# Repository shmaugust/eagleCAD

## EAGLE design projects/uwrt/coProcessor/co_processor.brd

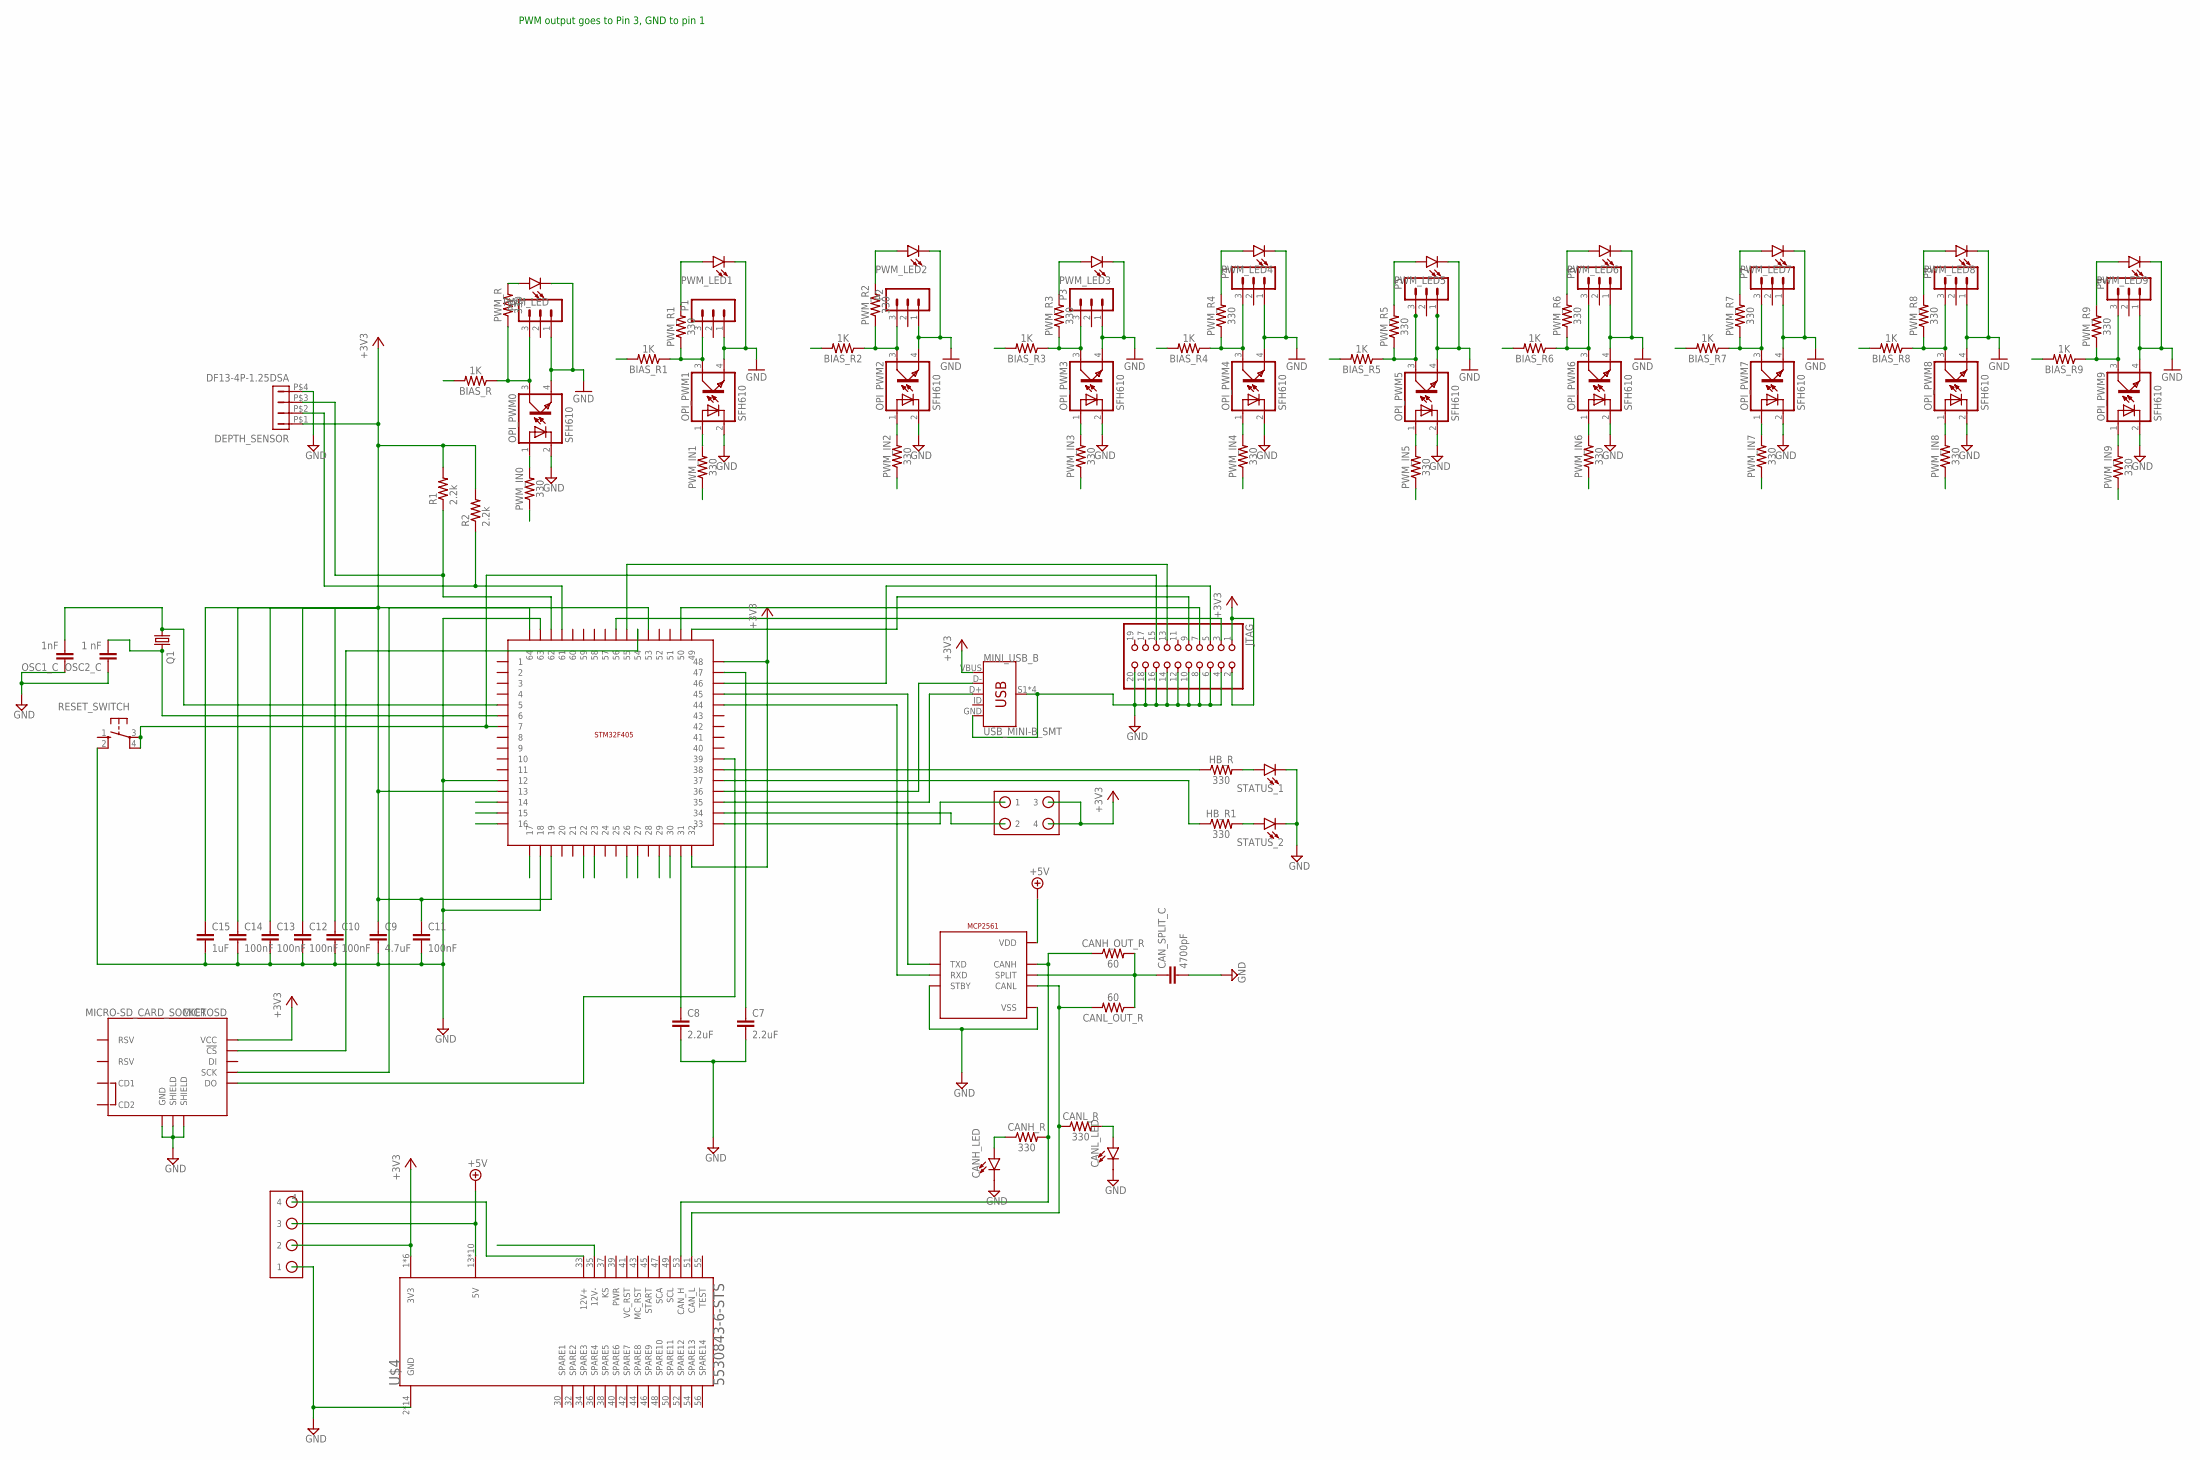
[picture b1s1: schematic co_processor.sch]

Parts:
BIAS_R, BIAS_R1, BIAS_R2, BIAS_R3, BIAS_R4, BIAS_R5, BIAS_R6, BIAS_R7, BIAS_R8, BIAS_R9: 1K; 0603
C7, C8: 2.2uF; C025-025X050
C9: 4.7uF; C025-025X050
C10, C11, C12, C13, C14: 100nF; C025-025X050
C15: 1uF; C025-025X050
CANH_LED: LED1206; LED-1206
CANH_OUT_R: 60; 0603
CANH_R: 330; 0603
CANL_LED: LED1206; LED-1206
CANL_OUT_R: 60; 0603
CANL_R: 330; 0603
CAN_SPLIT_C: 4700pF; C2.5-2
DEPTH_SENSOR: DF13-4P-1.25DSA
HB_R, HB_R1: 330; 0603
JTAG: PINHD-2X10; 2X10
MCP2561: MCP2561; SOIC8
MICROSD: MICRO-SD_CARD_SOCKET; MICRO-SD-SOCKET
MINI_USB_B: USB_MINI-B_SMT; USB-MINIB
OPI_PWM0, OPI_PWM1, OPI_PWM2, OPI_PWM3, OPI_PWM4, OPI_PWM5, OPI_PWM6, OPI_PWM7, OPI_PWM8, OPI_PWM9: SFH610; DIL04
OSC1_C: 1nF; C2.5-2
OSC2_C: 1 nF; C2.5-2
P0, P1, P2, P3, P4, P5, P6, P7, P8, P9: MA03-1
PWM_IN0, PWM_IN1, PWM_IN2, PWM_IN3, PWM_IN4, PWM_IN5, PWM_IN6, PWM_IN7, PWM_IN8, PWM_IN9: 330; 0603
PWM_LED, PWM_LED1, PWM_LED2, PWM_LED3, PWM_LED4, PWM_LED5, PWM_LED6, PWM_LED7, PWM_LED8, PWM_LED9: LED1206; LED-1206
PWM_R, PWM_R1, PWM_R2, PWM_R3, PWM_R4, PWM_R5, PWM_R6, PWM_R7, PWM_R8, PWM_R9: 330; 0603
Q1: CRYSTALHC49S; HC49/S
R1, R2: 2.2k; 0204/5
RESET_SWITCH: 10-XX; B3F-10XX
STATUS_1, STATUS_2: LED1206; LED-1206
STM32F405: STM32F405RG
SWITCHES: 39-30-1040; 5569-04A2
U$4: 5530843-6-STS; 5530843-6-BOARD
U$7: 70555-0003

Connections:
12V_OUT: BIAS_R.2, BIAS_R1.2, BIAS_R2.2, BIAS_R3.2, BIAS_R4.2, BIAS_R5.2, BIAS_R6.2, BIAS_R7.2, BIAS_R8.2, BIAS_R9.2, U$4.33 (12V+), U$7.4
+3V3: C9.1, C10.1, C11.1, C12.1, C13.1, C14.1, C15.1, DEPTH_SENSOR.P$1 (1), JTAG.1, JTAG.2, MICROSD.VCC, MINI_USB_B.VBUS, R1.2, R2.2, STM32F405.13, STM32F405.19, STM32F405.32, STM32F405.48, STM32F405.64, SWITCHES.1 (4), SWITCHES.2 (3), U$4.1 (3V3), U$4.3 (3V3), U$4.5 (3V3), U$4.7 (3V3), U$4.9 (3V3), U$4.11 (3V3), U$7.2
+5V: MCP2561.P$3 (VDD), U$4.13 (5V), U$4.15 (5V), U$4.17 (5V), U$4.19 (5V), U$4.21 (5V), U$4.23 (5V), U$4.25 (5V), U$4.27 (5V), U$4.29 (5V), U$4.31 (5V), U$7.3
CANH_LED: CANH_LED.A, CANH_R.1
CANH_OUT: CANH_OUT_R.1, CANH_R.2, MCP2561.P$7 (CANH), U$4.53 (CAN_H)
CANL_LED: CANL_LED.A, CANL_R.2
CANL_OUT: CANL_OUT_R.2, CANL_R.1, MCP2561.P$6 (CANL), U$4.51 (CAN_L)
CAN_RX: MCP2561.P$4 (RXD), STM32F405.44
CAN_SPLIT: CANH_OUT_R.2, CANL_OUT_R.1, CAN_SPLIT_C.1, MCP2561.P$5 (SPLIT)
CAN_TX: MCP2561.P$1 (TXD), STM32F405.45
GND: C7.2, C8.2, C9.2, C10.2, C11.2, C12.2, C13.2, C14.2, C15.2, CANH_LED.C, CANL_LED.C, CAN_SPLIT_C.2, DEPTH_SENSOR.P$4 (4), JTAG.4, JTAG.6, JTAG.8, JTAG.10, JTAG.12, JTAG.14, JTAG.16, JTAG.18, JTAG.20, MCP2561.P$2 (VSS), MCP2561.P$8 (STBY), MICROSD.GND, MICROSD.GND1 (SHIELD), MICROSD.GND3 (SHIELD), MINI_USB_B.GND, MINI_USB_B.S1 (SHIELD), MINI_USB_B.S2 (SHIELD), MINI_USB_B.S3 (SHIELD), MINI_USB_B.S4 (SHIELD), OPI_PWM0.2 (C), OPI_PWM1.2 (C), OPI_PWM2.2 (C), OPI_PWM3.2 (C), OPI_PWM4.2 (C), OPI_PWM5.2 (C), OPI_PWM6.2 (C), OPI_PWM7.2 (C), OPI_PWM8.2 (C), OPI_PWM9.2 (C), OSC1_C.1, OSC2_C.1, RESET_SWITCH.2 (S1), STATUS_1.C, STATUS_2.C, STM32F405.12, STM32F405.18, STM32F405.63, U$4.2 (GND), U$4.4 (GND), U$4.6 (GND), U$4.8 (GND), U$4.10 (GND), U$4.12 (GND), U$4.14 (GND), U$4.16 (GND), U$4.18 (GND), U$4.20 (GND), U$4.22 (GND), U$4.24 (GND), U$4.26 (GND), U$4.28 (GND), U$7.1
GND_ESC: OPI_PWM0.4 (EMIT), OPI_PWM1.4 (EMIT), OPI_PWM2.4 (EMIT), OPI_PWM3.4 (EMIT), OPI_PWM4.4 (EMIT), OPI_PWM5.4 (EMIT), OPI_PWM6.4 (EMIT), OPI_PWM7.4 (EMIT), OPI_PWM8.4 (EMIT), OPI_PWM9.4 (EMIT), P0.1, P1.1, P2.1, P3.1, P4.1, P5.1, P6.1, P7.1, P8.1, P9.1, PWM_LED.C, PWM_LED1.C, PWM_LED2.C, PWM_LED3.C, PWM_LED4.C, PWM_LED5.C, PWM_LED6.C, PWM_LED7.C, PWM_LED8.C, PWM_LED9.C
HB_OUT: HB_R.1, STM32F405.38
HB_OUT1: HB_R1.1, STM32F405.37
I2C_SCL: DEPTH_SENSOR.P$2 (2), R2.1, STM32F405.61
I2C_SDA: DEPTH_SENSOR.P$3 (3), R1.1, STM32F405.62
JTAG_RST: JTAG.3, STM32F405.56
JTAG_TCK: JTAG.9, STM32F405.49
JTAG_TDI: JTAG.5, STM32F405.50
JTAG_TDO: JTAG.13, STM32F405.55
JTAG_TMS: JTAG.7, STM32F405.46
KILL_SW: STM32F405.34, SWITCHES.3 (2)
unnamed: HB_R.2, STATUS_1.A
unnamed: HB_R1.2, STATUS_2.A
unnamed: OPI_PWM1.1 (A), PWM_IN1.2
unnamed: PWM_LED.A, PWM_R.2
unnamed: PWM_LED1.A, PWM_R1.2
unnamed: OPI_PWM3.1 (A), PWM_IN3.2
unnamed: OPI_PWM4.1 (A), PWM_IN4.2
unnamed: OPI_PWM5.1 (A), PWM_IN5.2
unnamed: PWM_LED2.A, PWM_R2.2
unnamed: PWM_LED3.A, PWM_R3.2
unnamed: OPI_PWM9.1 (A), PWM_IN9.2
unnamed: PWM_LED9.A, PWM_R9.2
unnamed: PWM_LED8.A, PWM_R8.2
unnamed: PWM_LED7.A, PWM_R7.2
unnamed: PWM_LED6.A, PWM_R6.2
unnamed: PWM_LED5.A, PWM_R5.2
unnamed: OPI_PWM6.1 (A), PWM_IN6.2
unnamed: OPI_PWM7.1 (A), PWM_IN7.2
unnamed: OPI_PWM8.1 (A), PWM_IN8.2
unnamed: PWM_LED4.A, PWM_R4.2
unnamed: OPI_PWM0.1 (A), PWM_IN0.2
unnamed: OPI_PWM2.1 (A), PWM_IN2.2
NRST: JTAG.15, RESET_SWITCH.3, RESET_SWITCH.4 (P1), STM32F405.7
OSC_IN: OSC1_C.2, Q1.1, STM32F405.5
OSC_OUT: OSC2_C.2, Q1.2, STM32F405.6
PWM0_BO: BIAS_R.1, OPI_PWM0.3 (COL), P0.3, PWM_R.1
PWM0_OUT: PWM_IN0.1, STM32F405.30
PWM1_BO: BIAS_R1.1, OPI_PWM1.3 (COL), P1.3, PWM_R1.1
PWM1_OUT: PWM_IN1.1, STM32F405.29
PWM2_BO: BIAS_R2.1, OPI_PWM2.3 (COL), P2.3, PWM_R2.1
PWM2_OUT: PWM_IN2.1, STM32F405.27
PWM3_BO: BIAS_R3.1, OPI_PWM3.3 (COL), P3.3, PWM_R3.1
PWM3_OUT: PWM_IN3.1, STM32F405.26
PWM4_BO: BIAS_R4.1, OPI_PWM4.3 (COL), P4.3, PWM_R4.1
PWM4_OUT: PWM_IN4.1, STM32F405.23
PWM5_BO: BIAS_R5.1, OPI_PWM5.3 (COL), P5.3, PWM_R5.1
PWM5_OUT: PWM_IN5.1, STM32F405.22
PWM6_BO: BIAS_R6.1, OPI_PWM6.3 (COL), P6.3, PWM_R6.1
PWM6_OUT: PWM_IN6.1, STM32F405.17
PWM7_BO: BIAS_R7.1, OPI_PWM7.3 (COL), P7.3, PWM_R7.1
PWM7_OUT: PWM_IN7.1, STM32F405.16
PWM8_BO: BIAS_R8.1, OPI_PWM8.3 (COL), P8.3, PWM_R8.1
PWM8_OUT: PWM_IN8.1, STM32F405.15
PWM9_BO: BIAS_R9.1, OPI_PWM9.3 (COL), P9.3, PWM_R9.1
PWM9_OUT: PWM_IN9.1, STM32F405.14
SDIO_CK: MICROSD.SCLK (SCK), STM32F405.53
SDIO_CMD: MICROSD.CS (!CS), STM32F405.54
SDIO_D0: MICROSD.DO, STM32F405.39
START_SW: STM32F405.33, SWITCHES.4 (1)
USB_DM: MINI_USB_B.D-, STM32F405.36
USB_DP: MINI_USB_B.D+, STM32F405.35
VCAP_1: C8.1, STM32F405.31
VCAP_2: C7.1, STM32F405.47

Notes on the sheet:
PWM output goes to Pin 3, GND to pin 1

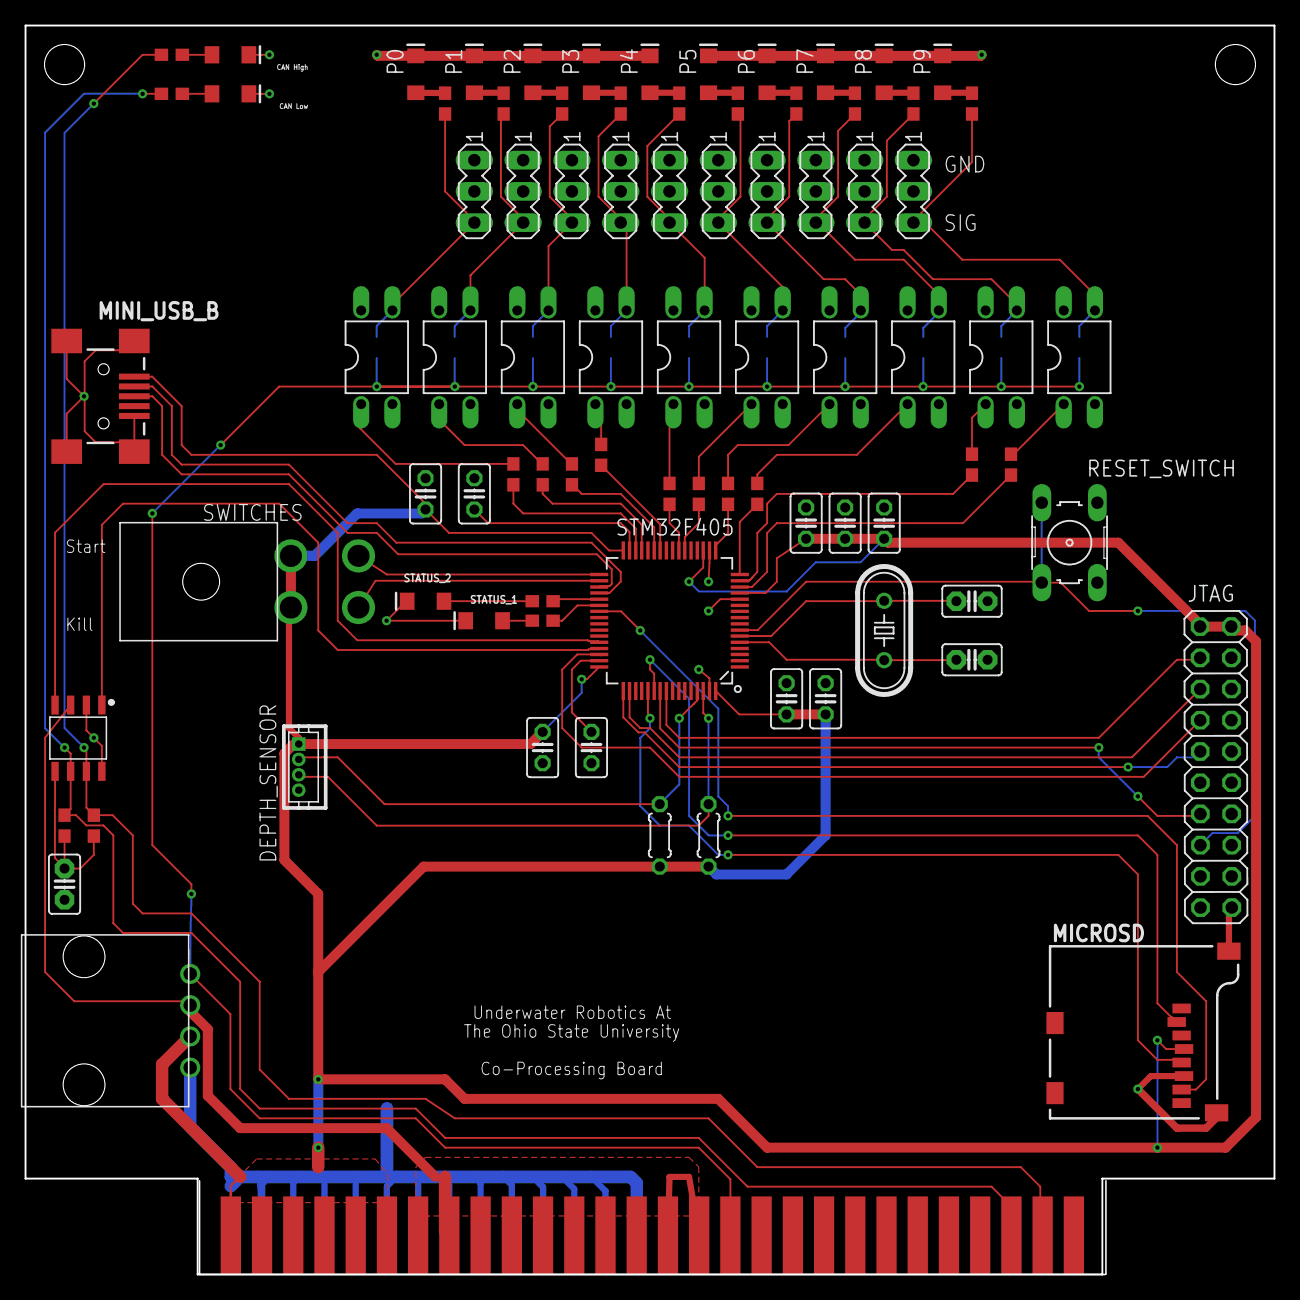
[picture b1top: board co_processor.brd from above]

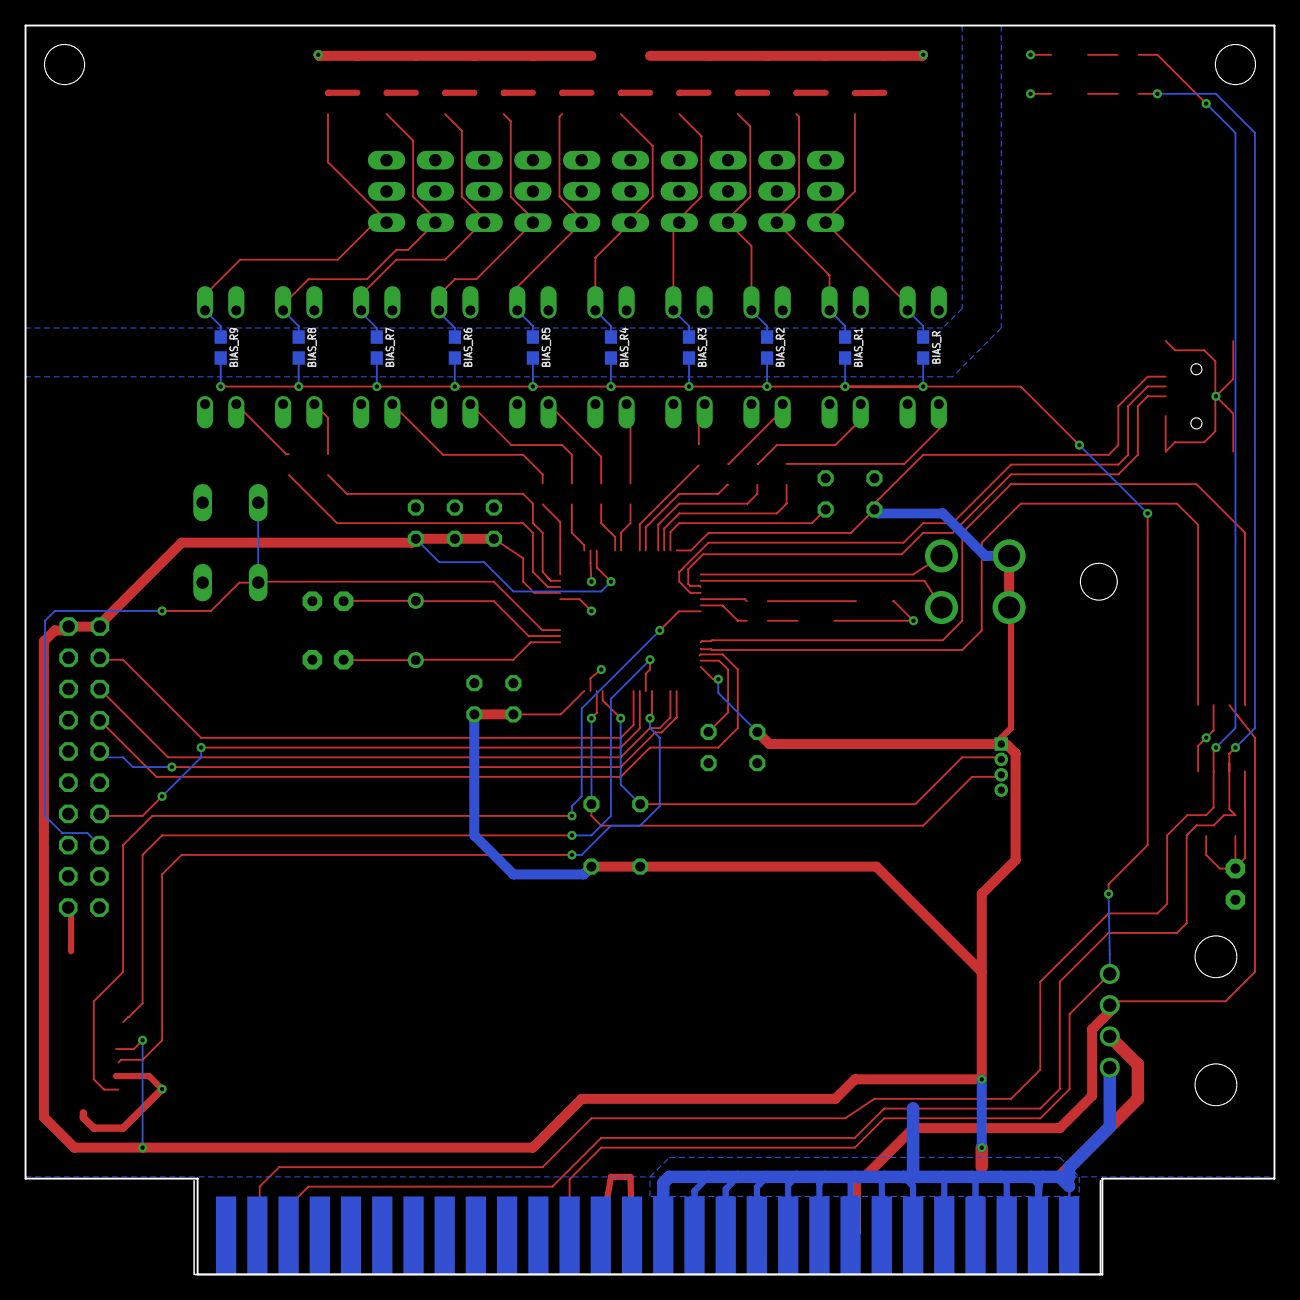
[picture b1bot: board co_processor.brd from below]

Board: 2 copper layers, 101.6 x 101.6 mm, 95 parts (10 on the bottom side), 75 nets.

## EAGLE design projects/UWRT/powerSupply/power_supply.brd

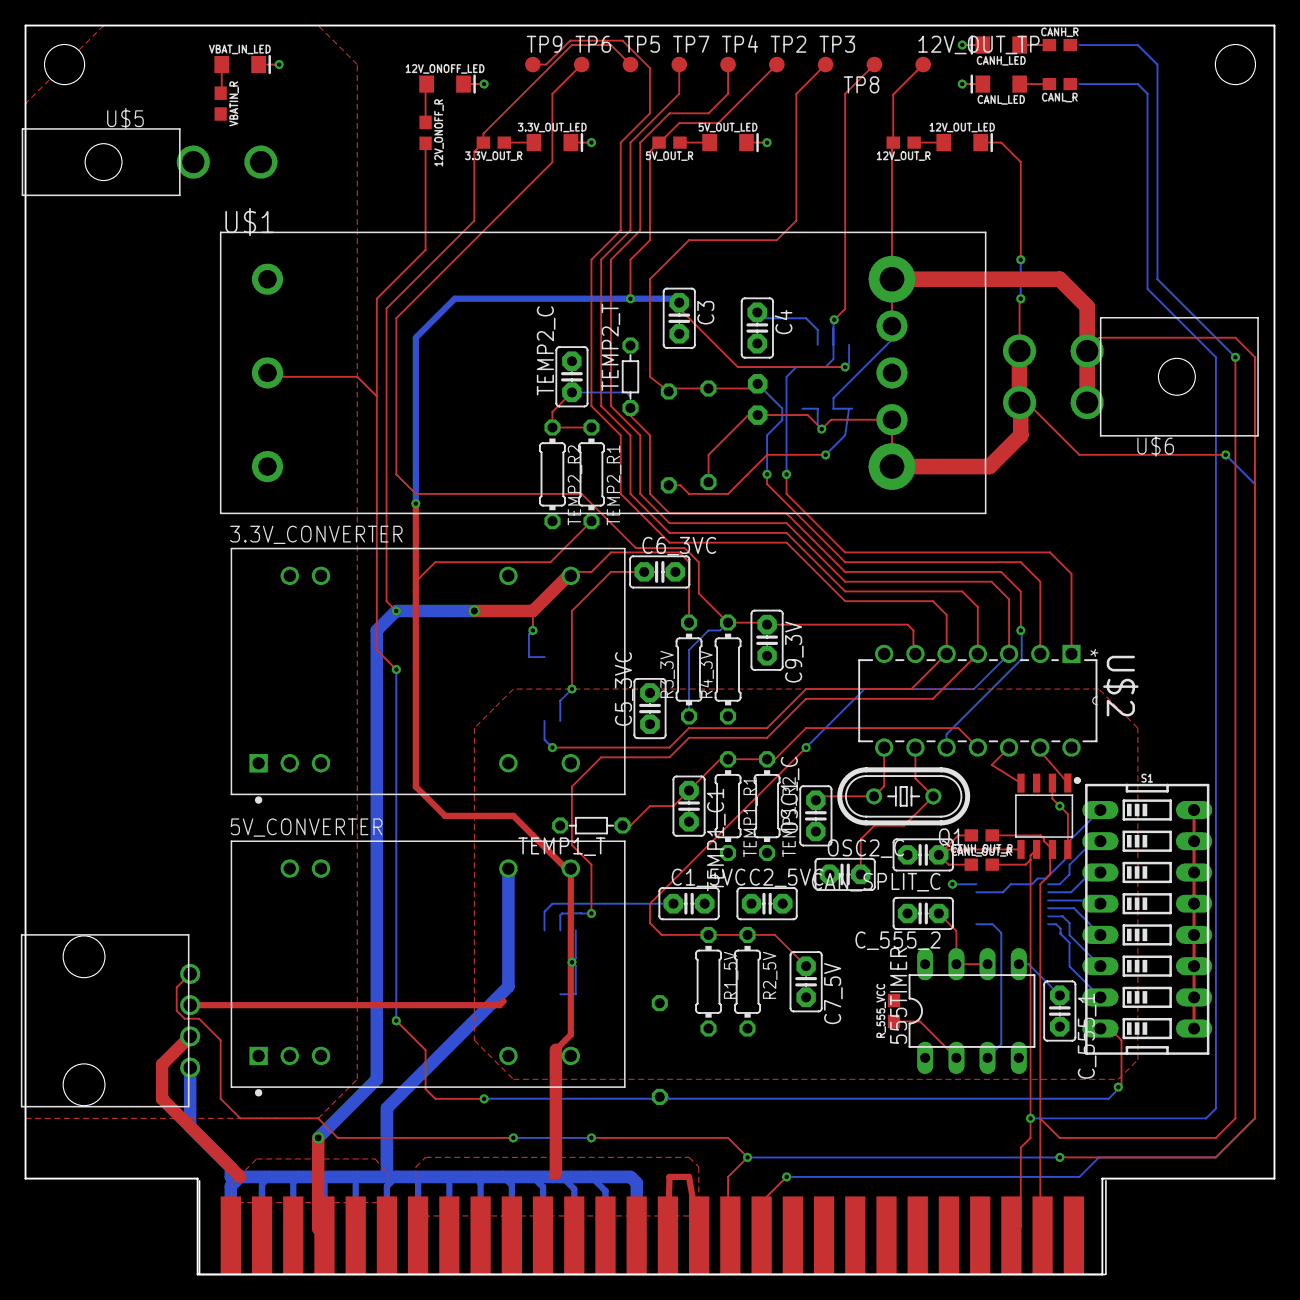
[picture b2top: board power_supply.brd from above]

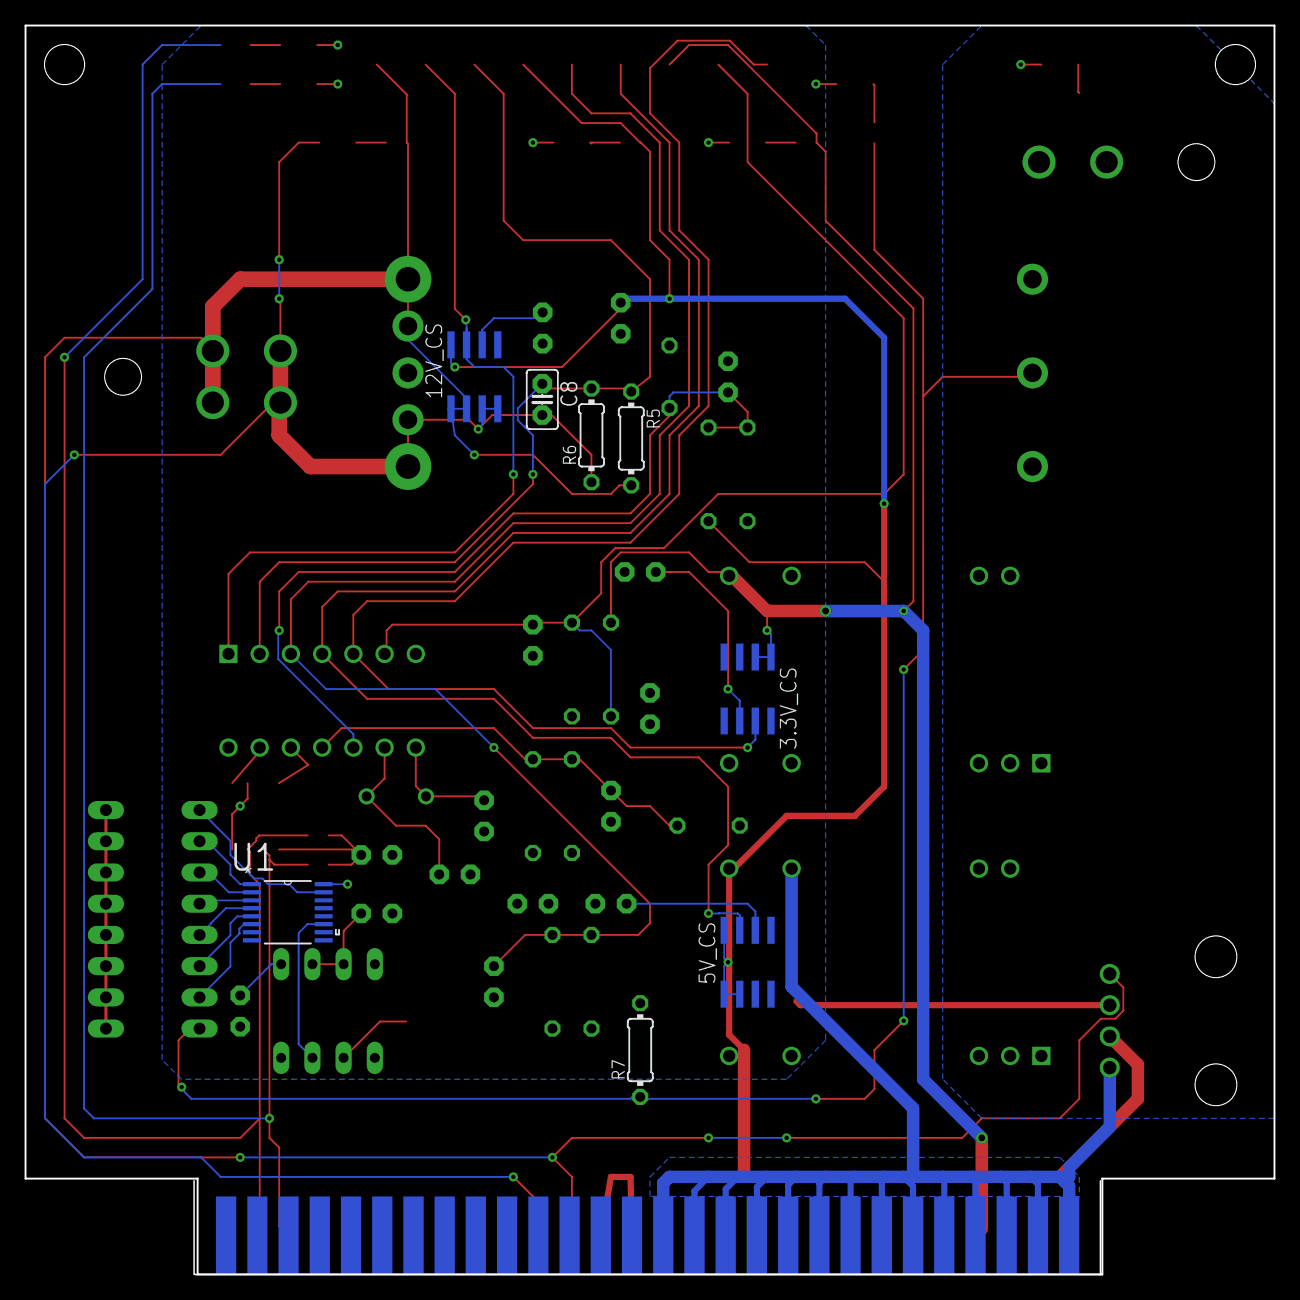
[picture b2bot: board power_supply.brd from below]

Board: 2 copper layers, 101.6 x 101.6 mm, 71 parts (8 on the bottom side), 44 nets.

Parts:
3.3V_CONVERTER: NCS12S1203C; CONV_NCS12S1203C
3.3V_CS, 5V_CS, 12V_CS: ACS712-LC; SOIC8
3.3V_OUT_LED, 5V_OUT_LED, 12V_ONOFF_LED, 12V_OUT_LED: LED-1206
3.3V_OUT_R, 5V_OUT_R, 12V_ONOFF_R, 12V_OUT_R: 330; 0603
5V_CONVERTER: NCS12S1205C; CONV_NCS12S1205C
12V_OUT_TP: PTR1B1,27; B1,27
555TIMER: NE555; DIL-08
C1_5VC, C4, C6_3VC: 1 nF; C2.5-2
C2_5VC, C3, C5_3VC, C7_5V, C8, C9_3V: 0.1 uF; C2.5-2
CANH_LED: LED-1206
CANH_OUT_R: 60; 0603
CANH_R: 330; 0603
CANL_LED: LED-1206
CANL_OUT_R: 60; 0603
CANL_R: 330; 0603
CAN_SPLIT_C: 4700pF; C2.5-2
C_555_1: 10nF; C2.5-2
C_555_2: 100 uF; C2.5-2
MCP2561: MCP2561; SOIC8
OSC1_C: 1nF; C2.5-2
OSC2_C: 1 nF; C2.5-2
Q1: HC49/S
R1_5V, R2_5V, R3_3V, R4_3V, R5, R6, R7: 0204/7
R_555_VCC: 10000; 0603
S1: DIPSWITCH-08
TEMP1_C1, TEMP2_C: 0.1 uF; C2.5-2
TEMP1_R1, TEMP1_R2, TEMP2_R1, TEMP2_R2: 0204/7
TEMP1_T, TEMP2_T: THERMISTOR-5; R-5
TP2, TP3, TP4, TP5, TP6, TP7, TP8, TP9: PTR1B1,27; B1,27
U1: SN74HC595PW; SOP65P640X120-16N
U$1: UIE48T10120
U$2: MCP25020-I/P; DIP254P762X432-14
U$4: 5530843-6-STS; 5530843-6-BOARD
U$5: 39-30-1020; 5569-02A2
U$6: 39-30-1040; 5569-04A2
U$7: 70555-0003
VBATIN_R: 330; 0603
VBAT_IN_LED: LED-1206

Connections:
3.3V_ANA_CUR_OUT: 3.3V_CS.7, TP9.TP, U$2.5
3.3V_OUT: 3.3V_CONVERTER.14, 3.3V_CS.1, 3.3V_CS.2, 3.3V_OUT_R.2, R3_3V.2, TP5.TP, U$4.1, U$4.3, U$4.5, U$4.7, U$4.9, U$4.11, U$7.2
3.3V_OUT_LED: 3.3V_OUT_LED.A, 3.3V_OUT_R.1
3V_VOL_ANA_OUT: C9_3V.1, R3_3V.1, R4_3V.2, TP6.TP, U$2.6
5V_CUR_ANA_OUT: 5V_CS.7, TP7.TP, U$2.4
5V_OUT_LED: 5V_OUT_LED.A, 5V_OUT_R.1
5V_VOL_ANA_OUT: C7_5V.1, R1_5V.1, R2_5V.1, TP4.TP, U$2.3
12V_CON_ONOFF: 12V_ONOFF_R.2, R7.1, S1.9, S1.10, S1.11, S1.12, S1.13, S1.14, S1.15, S1.16, U$1.ON/OFF
12V_CUR_ANA_OUT: 12V_CS.7, TP8.TP, U$2.1
12V_FILTER: 12V_CS.6, C4.1
12V_GND: 12V_CS.3, 12V_CS.4, 12V_OUT_LED.C, C8.2, R6.1, U$1.VOUT(-), U$1.VOUT_SENSE(-), U$4.35, U$6.3, U$6.4
12V_ONOFF_LED: 12V_ONOFF_LED.A, 12V_ONOFF_R.1
12V_OUT: 12V_CS.1, 12V_CS.2, 12V_OUT_R.2, 12V_OUT_TP.TP, R5.2, U$1.VOUT(+), U$1.VOUT_SENSE(+), U$4.33, U$6.1, U$6.2, U$7.4
12V_OUT_LED: 12V_OUT_LED.A, 12V_OUT_R.1
12V_VOL_ANA_OUT: C8.1, R5.1, R6.2, TP3.TP, U$2.2
555_CON: 555TIMER.5, C_555_1.1
555_TREDIS: 555TIMER.6, 555TIMER.7, C_555_2.1
555_TRIG: 555TIMER.2, R_555_VCC.1
CANH_LED: CANH_LED.A, CANH_R.1
CANH_OUT: CANH_OUT_R.1, CANH_R.2, MCP2561.P$7, U$4.53
CANL_LED: CANL_LED.A, CANL_R.2
CANL_OUT: CANL_OUT_R.2, CANL_R.1, MCP2561.P$6, U$4.51
CAN_SPLIT: CANH_OUT_R.2, CANL_OUT_R.1, CAN_SPLIT_C.1, MCP2561.P$5
FILTER_3V: 3.3V_CS.6, C6_3VC.1
FILTER_5V: 5V_CS.6, C1_5VC.1
GND: 3.3V_CONVERTER.16, 3.3V_CS.3, 3.3V_CS.4, 3.3V_CS.5, 3.3V_OUT_LED.C, 5V_CONVERTER.16, 5V_CS.3, 5V_CS.4, 5V_CS.5, 5V_OUT_LED.C, 12V_CS.5, 12V_ONOFF_LED.C, 555TIMER.1, C1_5VC.2, C2_5VC.2, C3.2, C4.2, C5_3VC.2, C6_3VC.2, C7_5V.2, C9_3V.2, CANH_LED.C, CANL_LED.C, CAN_SPLIT_C.2, C_555_1.2, C_555_2.2, MCP2561.P$2, MCP2561.P$8, OSC1_C.1, OSC2_C.1, R2_5V.2, R4_3V.1, S1.8, TEMP1_C1.2, TEMP1_R2.2, TEMP1_T.2, TEMP2_C.2, TEMP2_R2.2, TEMP2_T.2, U1.8, U$2.7, U$4.2, U$4.4, U$4.6, U$4.8, U$4.10, U$4.12, U$4.14, U$4.16, U$4.18, U$4.20, U$4.22, U$4.24, U$4.26, U$4.28, U$7.1
unnamed: MCP2561.P$4, U$2.12
unnamed: MCP2561.P$1, U$2.13
NAND1: S1.1, U1.15
NAND2: S1.2, U1.1
NAND3: S1.3, U1.2
NAND4: S1.4, U1.3
NAND5: S1.5, U1.4
NAND6: S1.6, U1.5
NAND7: S1.7, U1.6
OSC1: OSC1_C.2, Q1.2, U$2.8
OSC2: OSC2_C.2, Q1.1, U$2.9
OUT555: 555TIMER.3, U1.11
TEMP1_ANA_OUT: TEMP1_C1.1, TEMP1_R1.1, TEMP1_R2.1, TEMP1_T.1, U$2.11
TEMP2_ANA_OUT: TEMP2_C.1, TEMP2_R1.1, TEMP2_R2.1, TEMP2_T.1, U$2.10
VBAT_IN_LED: VBATIN_R.1, VBAT_IN_LED.A
VCC: 3.3V_CS.8, 5V_CONVERTER.14, 5V_CS.1, 5V_CS.2, 5V_CS.8, 5V_OUT_R.2, 12V_CS.8, 555TIMER.4, 555TIMER.8, C2_5VC.1, C3.1, C5_3VC.1, MCP2561.P$3, R1_5V.2, R7.2, R_555_VCC.2, TEMP1_R1.2, TEMP2_R1.2, TP2.TP, U1.16, U$2.14, U$4.13, U$4.15, U$4.17, U$4.19, U$4.21, U$4.23, U$4.25, U$4.27, U$4.29, U$4.31, U$7.3
V_BAT_BAL+: 3.3V_CONVERTER.22, 3.3V_CONVERTER.23, 5V_CONVERTER.22, 5V_CONVERTER.23, U$1.VIN(+), U$5.2, VBATIN_R.2
V_BAT_BAL-: 3.3V_CONVERTER.2, 3.3V_CONVERTER.3, 5V_CONVERTER.2, 5V_CONVERTER.3, U$1.VIN(-), U$5.1, VBAT_IN_LED.C

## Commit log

2017-07-06 Initial Commit
    added the initial commit
2017-07-07 Initial commit of the power supply board.
2017-07-07 Editted timing section of board
2017-07-07 Removed the *.*#1 files
2017-07-12 Updating with new CAN stuff
2017-07-16 Updated semi - final design
2017-07-18 Error checking, version 1.0 to print
2017-07-18 Updated to add the gerbers
2017-07-18 Clean up PS gerbers, initial commit of coPro
2017-07-18 Merged template with coPro connections
2017-07-19 Added coPro decoupling power stuff
2017-07-19 No frills processing board revision 1.0.0
2017-07-19 Minor touchups, fixed fragmenting GND plane
2017-07-19 Clean up JTAG traces
2017-07-19 Fixing DRC errors and approving others
2017-07-20 No frills Co Processing board rev 1.1.0
2017-08-10 Small updates before transfer of ownership

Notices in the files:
parts and their libraries:
SparkFun-Switches: Licensing: Creative Commons ShareAlike 4.0 International - https://creativecommons.org/licenses/by-sa/4.0
